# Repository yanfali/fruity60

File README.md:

## The Fruity60 Keyboard

A 60% PCB compatible with the [Adafruit Bluefruit BLE 32u4](https://github.com/adafruit/Adafruit-Feather-32u4-Bluefruit-LE-PCB).

Only supports 1 layout (tsangan), PCB mounted switches.

Primarily designed for fun, to learn [KICAD](http://www.kicad.org/)
and give back to the keyboard community in educational material.
If you find this design useful, I ask you to please
[donate](https://donorbox.org/qmk) to [QMK](https://qmk.fm), as it is the
amazing community and enthusiastic support of it's members that
helped me to design this.

Files released under https://creativecommons.org/licenses/by-nc-sa/4.0/

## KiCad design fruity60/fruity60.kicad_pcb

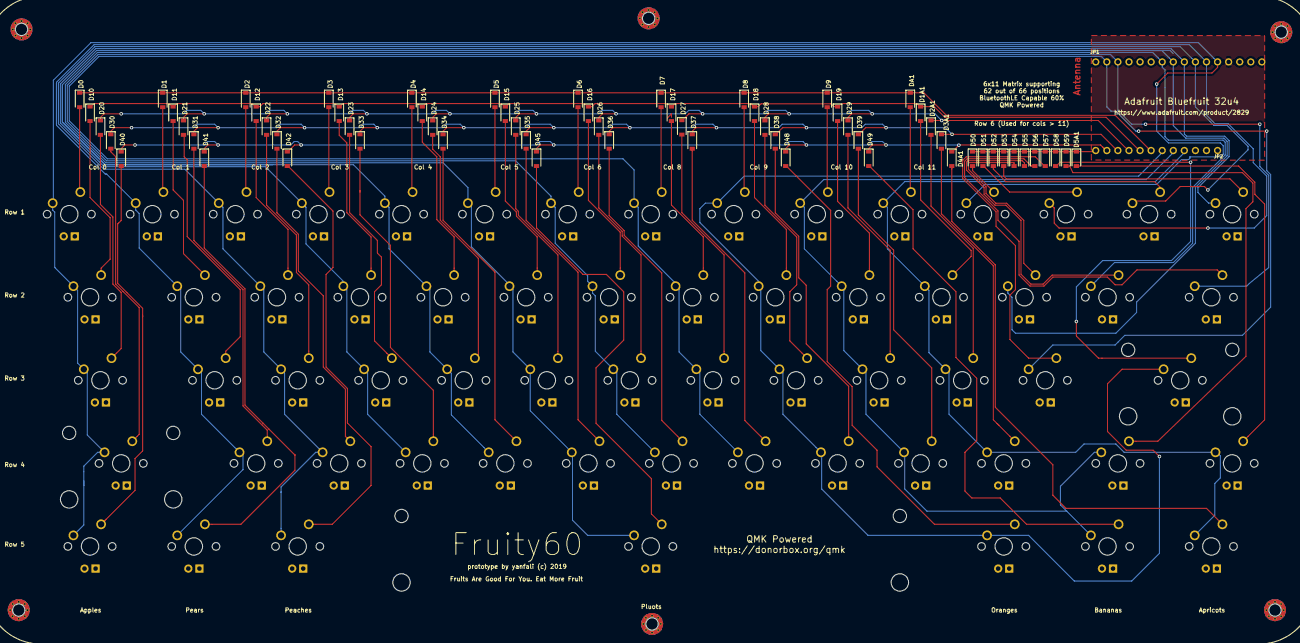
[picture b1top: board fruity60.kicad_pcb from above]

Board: 2 copper layers, 126 parts (0 on the bottom side), 79 nets.

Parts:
D0, D1, D1A1, D2, D2A1, D3, D3A1, D4, D4A1, D5, D5A1, D6, D7, D8, D9, D10, D11, D12, D13, D14, D15, D16, D17, D18, D19, D20, D21, D22, D23, D24, D25, D26, D27, D28, D29, D30, D31, D32, D33, D34, D35, D36, D37, D38, D39, D40, D41, D42, D45, D48, D49, D50, D51, D52, D53, D54, D55, D56, D57, D58, D59: D_Small; D_SOD-123
DA1: D_Small; D_SOD-123
JP1: HEADER-1X16ROUND; 1X16_ROUND
JP2: HEADER-1X12; 1X12_ROUND
MX0: K00; MXOnly-1U
MX0A1: K0A; MXOnly-1U
MX1: K01; MXOnly-1U
MX1A1: K1A; MXOnly-1U
MX2: K02; MXOnly-1U
MX2A1: K2A; MXOnly-1U
MX3: K03; MXOnly-1U
MX3A1: K3A; MXOnly-1U
MX4: K04; MXOnly-1U
MX4A1: K4A; MXOnly-1.5U
MX5: K05; MXOnly-1U
MX5A1: K5A; MXOnly-1U
MX6: K06; MXOnly-1U
MX7: K07; MXOnly-1U
MX8: K08; MXOnly-1U
MX9: K09; MXOnly-1U
MX10: K10; MXOnly-1.5U
MX11: K11; MXOnly-1U
MX12: K12; MXOnly-1U
MX13: K13; MXOnly-1U
MX14: K14; MXOnly-1U
MX15: K15; MXOnly-1U
MX16: K16; MXOnly-1U
MX17: K17; MXOnly-1U
MX18: K18; MXOnly-1U
MX19: K19; MXOnly-1U
MX20: K20; MXOnly-1.75U
MX21: K21; MXOnly-1U
MX22: K22; MXOnly-1U
MX23: K23; MXOnly-1U
MX24: K24; MXOnly-1U
MX25: K25; MXOnly-1U
MX26: K26; MXOnly-1U
MX27: K27; MXOnly-1U
MX28: K28; MXOnly-1U
MX29: K29; MXOnly-1U
MX30: K30; MXOnly-2.25U
MX31: K31; MXOnly-1U
MX32: K32; MXOnly-1U
MX33: K33; MXOnly-1U
MX34: K34; MXOnly-1U
MX35: K35; MXOnly-1U
MX36: K36; MXOnly-1U
MX37: K37; MXOnly-1U
MX38: K38; MXOnly-1U
MX39: K39; MXOnly-1U
MX40: K40; MXOnly-1.5U
MX41: K41; MXOnly-1U
MX42: K42; MXOnly-1.5U
MX45: K45; MXOnly-7U
MX48: K48; MXOnly-1.5U
MX49: K49; MXOnly-1U
MX50: K50; MXOnly-1U
MX51: K51; MXOnly-1U
MX52: K52; MXOnly-1U
MX53: K53; MXOnly-1U
MX54: K54; MXOnly-1U
MX55: K55; MXOnly-1U
MX56: K56; MXOnly-1.5U
MX57: K57; MXOnly-1U
MX58: K58; MXOnly-2.25U
MX59: K59; MXOnly-1.75U

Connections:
B5: D1A1.1, D10.1, D11.1, D12.1, D13.1, D14.1, D15.1, D16.1, D17.1, D18.1, D19.1, JP2.8
B6: D0.1, D1.1, D2.1, D3.1, D4.1, D5.1, D6.1, D7.1, D8.1, D9.1, DA1.1, JP2.7
B7: JP2.6, MX8.1, MX18.1, MX28.1, MX38.1, MX48.1, MX58.1
C6: D3A1.1, D30.1, D31.1, D32.1, D33.1, D34.1, D35.1, D36.1, D37.1, D38.1, D39.1, JP2.10
C7: JP2.4, MX0A1.1, MX1A1.1, MX2A1.1, MX3A1.1, MX4A1.1, MX5A1.1
D0: D4A1.1, D40.1, D41.1, D42.1, D45.1, D48.1, D49.1, JP2.11
D1: D5A1.1, D50.1, D51.1, D52.1, D53.1, D54.1, D55.1, D56.1, D57.1, D58.1, D59.1, JP2.12
D2: JP1.3, MX6.1, MX16.1, MX26.1, MX36.1, MX56.1
D3: JP1.2, MX7.1, MX17.1, MX27.1, MX37.1, MX57.1
D6: JP2.5, MX9.1, MX19.1, MX29.1, MX39.1, MX49.1, MX59.1
D7: D2A1.1, D20.1, D21.1, D22.1, D23.1, D24.1, D25.1, D26.1, D27.1, D28.1, D29.1, JP2.9
F0: JP1.7, MX5.1, MX15.1, MX25.1, MX35.1, MX45.1, MX55.1
F1: JP1.8, MX4.1, MX14.1, MX24.1, MX34.1, MX54.1
F4: JP1.9, MX3.1, MX13.1, MX23.1, MX33.1, MX53.1
F5: JP1.10, MX2.1, MX12.1, MX22.1, MX32.1, MX42.1, MX52.1
F6: JP1.11, MX1.1, MX11.1, MX21.1, MX31.1, MX41.1, MX51.1
F7: JP1.12, MX0.1, MX10.1, MX20.1, MX30.1, MX40.1, MX50.1
unnamed: D0.2, MX0.2
unnamed: D1.2, MX1.2
unnamed: D1A1.2, MX1A1.2
unnamed: D2.2, MX2.2
unnamed: D2A1.2, MX2A1.2
unnamed: D3.2, MX3.2
unnamed: D3A1.2, MX3A1.2
unnamed: D4.2, MX4.2
unnamed: D4A1.2, MX4A1.2
unnamed: D5.2, MX5.2
unnamed: D5A1.2, MX5A1.2
unnamed: D6.2, MX6.2
unnamed: D7.2, MX7.2
unnamed: D8.2, MX8.2
unnamed: D9.2, MX9.2
unnamed: D10.2, MX10.2
unnamed: D11.2, MX11.2
unnamed: D12.2, MX12.2
unnamed: D13.2, MX13.2
unnamed: D14.2, MX14.2
unnamed: D15.2, MX15.2
unnamed: D16.2, MX16.2
unnamed: D17.2, MX17.2
unnamed: D18.2, MX18.2
unnamed: D19.2, MX19.2
unnamed: D20.2, MX20.2
unnamed: D21.2, MX21.2
unnamed: D22.2, MX22.2
unnamed: D23.2, MX23.2
unnamed: D24.2, MX24.2
unnamed: D25.2, MX25.2
unnamed: D26.2, MX26.2
unnamed: D27.2, MX27.2
unnamed: D28.2, MX28.2
unnamed: D29.2, MX29.2
unnamed: D30.2, MX30.2
unnamed: D31.2, MX31.2
unnamed: D32.2, MX32.2
unnamed: D33.2, MX33.2
unnamed: D34.2, MX34.2
unnamed: D35.2, MX35.2
unnamed: D36.2, MX36.2
unnamed: D37.2, MX37.2
unnamed: D38.2, MX38.2
unnamed: D39.2, MX39.2
unnamed: D40.2, MX40.2
unnamed: D41.2, MX41.2
unnamed: D42.2, MX42.2
unnamed: D45.2, MX45.2
unnamed: D48.2, MX48.2
unnamed: D49.2, MX49.2
unnamed: D50.2, MX50.2
unnamed: D51.2, MX51.2
unnamed: D52.2, MX52.2
unnamed: D53.2, MX53.2
unnamed: D54.2, MX54.2
unnamed: D55.2, MX55.2
unnamed: D56.2, MX56.2
unnamed: D57.2, MX57.2
unnamed: D58.2, MX58.2
unnamed: D59.2, MX59.2
unnamed: DA1.2, MX0A1.2

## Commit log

2019-10-02 Add submodules
    ignore mac
    Renamed wires on left side
    Updated right side
    Use tags to wire ports
    Use global tags to hook up headers to matrix
    Rename untitled
2019-10-02 Add footprints
2019-10-02 fix up key sizes
2019-10-02 Basic layout of switches
2019-10-02 move some diodes around
2019-10-02 flip diodes. Thanks Skully
2019-10-02 Align diodes better
2019-10-02 Line up diodes for more pleasing look
2019-10-02 Clean ups
2019-10-02 Use 2.54 straight headers not angled
2019-10-02 Routing weirdness
    May need to change footprint for diodes
2019-10-03 progress
2019-10-03 10 unconnected10 unconnected10 unconnected10 unconnected10 unconnected10 unconnected10 unconnected10 unconnected10 unconnected10 unconnected
2019-10-03 Update with all nets
2019-10-03 first milestone
2019-10-03 m2 holes
2019-10-03 Add some silkscreen
2019-10-03 silkscreen additions
2019-10-03 Add matrix labels to switch positions
2019-10-03 restore power and gnd
2019-10-03 Add GND copper pour under the MCU
2019-10-03 Update schematic and silkscreen
2019-10-04 Add LICENSE
2019-10-04 Adjust copper so it isn't so close to drilling
2019-10-04 small tweaks
2019-10-04 holes went missing
2019-10-05 Clean up some more traces
2019-10-05 more clean ups
2019-10-08 Add README
2019-10-11 Move antenna keep out
2021-11-10 Update README.md
    https://forum.kicad.info/t/warning-avoid-all-links-to-kicad-pcb-org-use-kicad-org/31521

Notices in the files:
fruity60/fruity60.kicad_pcb:
prototype by yanfali (c) 2019
